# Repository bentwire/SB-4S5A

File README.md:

# SB-4S5A
4S1P 5000mAh smart battery

BOM: https://octopart.com/bom-tool/Ozuqnvew

![Image](https://lh3.googleusercontent.com/idjTSfCK8nfJFQzJIe7masI_trXQ7SMNvU6aqpUEBDsLIDIV-Hx3-JUPBGiGlPwAxTNEt7CckAo6dX-KWBZ0Mj_Hy6Guh6XXaXnfHWQ1HlrcL2ksQrWs3JgNRiBP9fyepqlfmhmZ2Kqe8utfv8-hr5f317K1JAQZiNnnJVtptgWgTnRBBOKp0zHjc3gDmaQTty2snsGGvR-t9d62PkFt3sAev27TS6WXzIwooHEbv2O3aN5GzwUc1_t97cg4gHyUgt0wO-D-wl_EM5B_Wx8xKgb3qa49QhaQvJhumIF56lDGn5g6sMpIpR3Uu-dUa1wRXa-HVk5tHxTNSXTCNnU1kgC_ebQERQPmjxoH67TADfJSTNa7XRiODJmf_CTr2TFzn8DMkGfC8BoBJ0X80usX03oGiI0V0uVGz-C7VfemFuEn6kE7K-gLMqWdNlwAt6iFMoFxGl0MOFubE6W7V08FnX0HrfcozMMg8dFBLveCm-QEvQhAoUhDco0joryzj_BHuwoiUDw_kgubxxIr_FZ4HCkC-sIuyp77qNHq5hAkarBPJ5yDwpvwfY6QkSCwr4eLbbmDiR7ImRQkwWTvxxCPkVSV9cAZq1OyEo_i0pI=w680-h916-no)

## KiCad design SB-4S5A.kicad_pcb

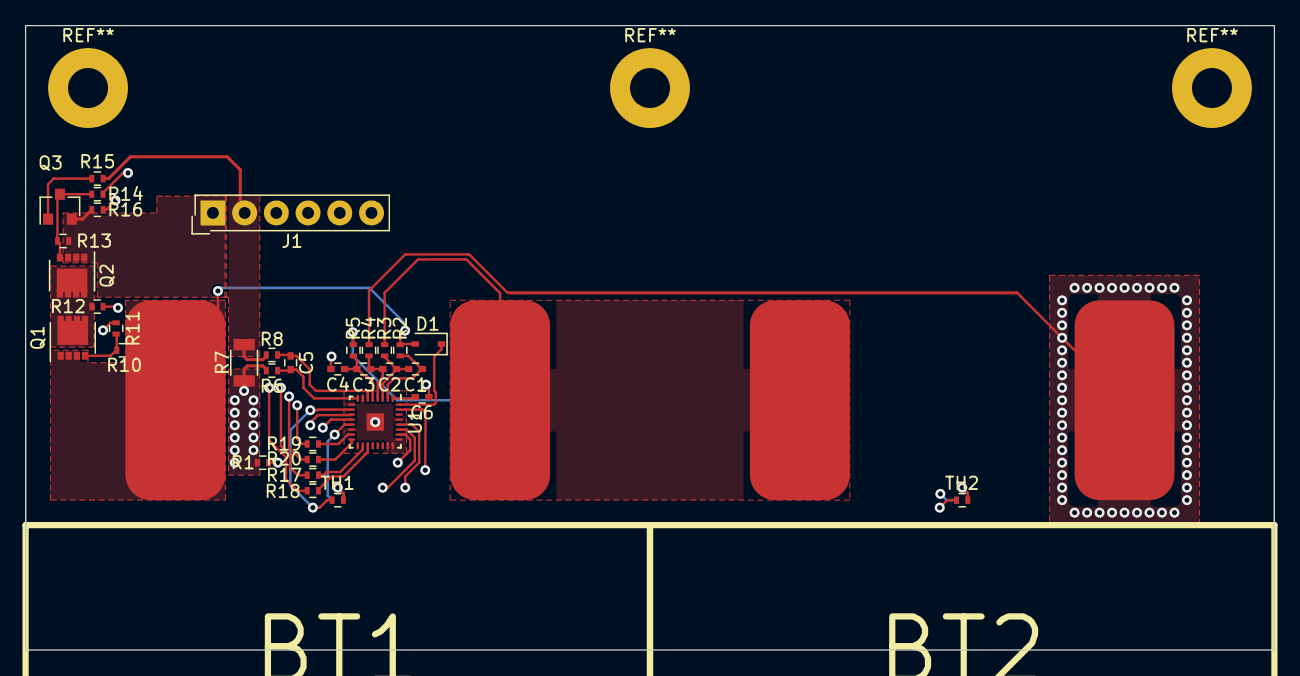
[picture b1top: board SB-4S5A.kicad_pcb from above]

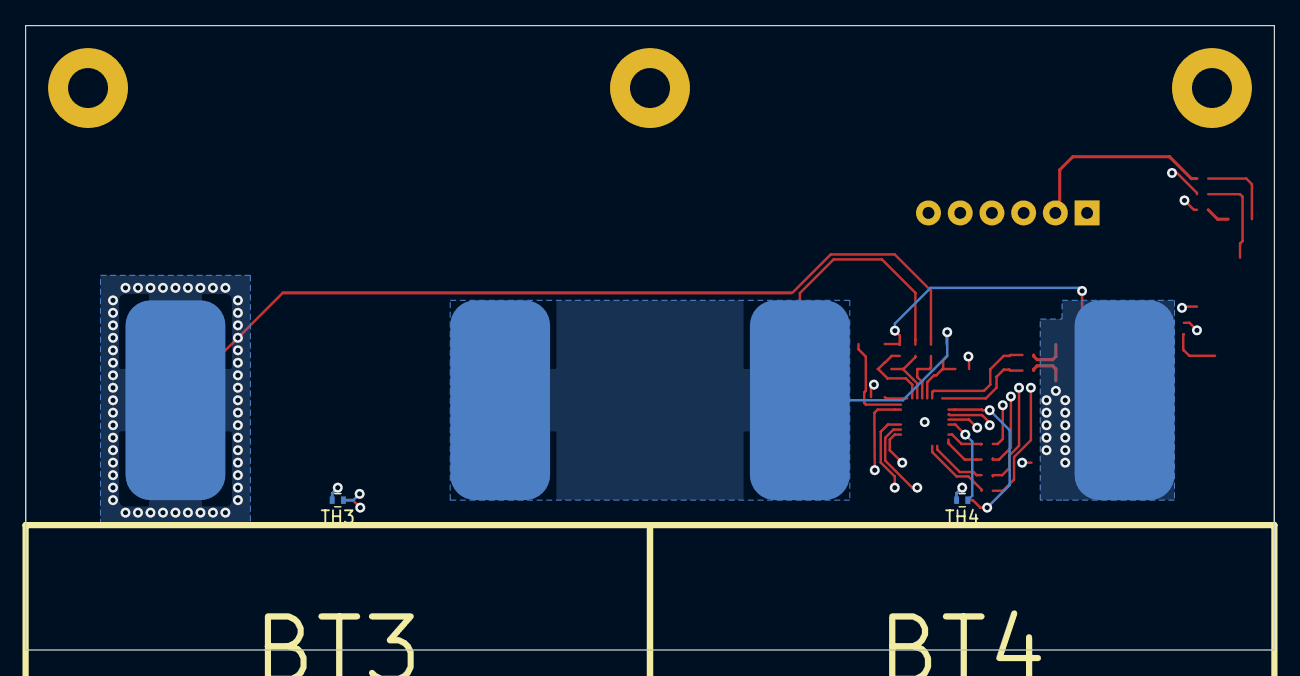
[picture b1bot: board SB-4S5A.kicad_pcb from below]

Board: 4 copper layers, 100.0 x 50.0 mm, 39 parts (4 on the bottom side), 36 nets.

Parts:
BT1, BT2, BT3, BT4: 3.7v; 105070
C1, C2, C3, C4, C5: 0.1u; C_0402
C6: 2.2u; C_0402
D1: BAT54HT1G; D_SOD-323
J1: LEMO6; SL-106-X-XX_1x06
Q1, Q2: CSD17308Q3; VSON-8_3.3x3.3mm_Pitch0.65mm_NexFET
Q3: 2N7002; SOT-23
R1: NET-TIE; R_0402
R2, R3, R4, R5, R6, R8, R12, R17, R18, R19, R20: 100R; R_0402
R7: 0.001R; R_1206
R10, R13: 10M; R_0402
R11, R14: 5.1K; R_0402
R15, R16: 10K; R_0402
TH1, TH2, TH3, TH4: 10K; R_0402
U1: bq40z50-r2; QFN-32_EP_3.8x3.8_Pitch0.4mm

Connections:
/BAT: D1.1, U1.32
/BAT+: BT1.1, D1.2, Q1.1, Q1.2, Q1.3, R2.1, R10.2
/BAT-: BT4.2, R1.1, R6.1, R7.2
/BTP_INT: J1.6, R19.2
/BTP_INT_: R19.1, U1.15
/CHG: R11.1, U1.31
/CHG_G: Q1.4, R10.1, R11.2
/DSG: R14.1, U1.28
/DSG_G: Q2.4, Q3.3, R13.1, R14.2
/MID: Q1.5, Q2.5, R12.2
/PACK: R16.2, U1.27
/PBI: C6.1, U1.1
/SMBC: J1.3, R18.2
/SMBC_: R18.1, U1.19
/SMBD: J1.4, R17.2
/SMBD_: R17.1, U1.18
/SRN: C5.1, R8.2, U1.6
/SRP: C5.2, R6.2, U1.8
/VC1: C3.2, C4.1, R5.2, U1.5
/VC1A: BT3.2, BT4.1, R5.1
/VC2: C2.2, C3.1, R4.2, U1.4
/VC2A: BT2.2, BT3.1, R4.1
/VC3: C1.2, C2.1, R3.2, U1.3
/VC3A: BT1.2, BT2.1, R3.1
/VC4: C1.1, R2.2, U1.2
/_VCC_: R12.1, U1.26
/~PRES/SHDN~_: R20.1, U1.16
/~PRES~: J1.5, R20.2
GNDD: C4.2, C6.2, R1.2, TH1.2, TH2.2, TH3.2, TH4.2, U1.7, U1.9, U1.14, U1.23, U1.24, U1.25, U1.29, U1.33
unnamed: Q3.1, R15.1
unnamed: TH1.1, U1.10
unnamed: TH2.1, U1.11
unnamed: TH3.1, U1.12
unnamed: TH4.1, U1.13
PACK+: J1.1, Q2.1, Q2.2, Q2.3, Q3.2, R13.2, R16.1
PACK-: J1.2, R7.1, R8.1, R15.2

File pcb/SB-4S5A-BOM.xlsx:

Qty | Line Item | Manufacturer | MPN | Octopart URL | Schematic Reference | Internal Part Number | Description | Total Qty (@ Batch Size: 10) | SKU | SKU | Packaging | Packaging | Unit Price (@ Batch Size: 10) | Unit Price (@ Batch Size: 10) | In Stock | In Stock | MOQ | MOQ | URL | URL | Distributor [Custom] | SKU [Custom] | Packaging [Custom] | Unit Price (@ Batch Size: 10) [Custom] | Line Total [Custom] | Batch Total [Custom] | In Stock [Custom] | MOQ [Custom] | URL [Custom] | Notes
 |  |  |  |  |  |  |  |  | Digi-Key | Mouser | Digi-Key | Mouser | Digi-Key | Mouser | Digi-Key | Mouser | Digi-Key | Mouser | Digi-Key | Mouser
2 | CSD17308Q3 | Texas Instruments | CSD17308Q3 | https://octopart.com/csd17308q3-texas+instruments-18530280 | Q1,Q2 |  |  | 20 | 296-27210-1-ND | CSD17308Q3 | Cut Tape |  | 0.904 | 0.676 | 23856 | 56 | 1 |  | https://octopart.com/click/track?country=US&ak=68b25f31&sig=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 | https://octopart.com/click/track?country=US&ak=68b25f31&sig=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 | Mouser | CSD17308Q3 |  | 0.676 | 1.352 | 13.52 | 56 |  | https://octopart.com/click/track?country=US&ak=68b25f31&sig=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
1 | BQ40Z50RSMT-R1 | Texas Instruments | BQ40Z50RSMT-R1 | https://octopart.com/bq40z50rsmt-r1-texas+instruments-60770459 | U1 |  |  | 10 | 296-42424-1-ND | BQ40Z50RSMT-R1 | Cut Tape |  | 5.379 | 5.79 | 0 | 8385 | 1 |  | https://octopart.com/click/track?country=US&ak=68b25f31&sig=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 | https://octopart.com/click/track?country=US&ak=68b25f31&sig=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 | Digi-Key | 296-42424-1-ND | Cut Tape | 5.379 | 5.379 | 53.79 | 0 | 1 | https://octopart.com/click/track?country=US&ak=68b25f31&sig=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
1 | 0.001 ohm 1% 1206 | Welwyn | LRMAM1206-R001FT5 | https://octopart.com/lrmam1206-r001ft5-welwyn-46392712 | R7 |  |  | 10 | 985-1544-1-ND | LRMAM1206-R001FT5 | Cut Tape |  | 0.404 | 0.38 | 5193 | 8269 | 1 |  | https://octopart.com/click/track?country=US&ak=68b25f31&sig=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 | https://octopart.com/click/track?country=US&ak=68b25f31&sig=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 | Mouser | LRMAM1206-R001FT5 |  | 0.38 | 0.38 | 3.8 | 8269 |  | https://octopart.com/click/track?country=US&ak=68b25f31&sig=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
2 | 10K 1% 0402 | Yageo | RC0402FR-0710KL | https://octopart.com/rc0402fr-0710kl-yageo-55458461 | R15,R16 |  |  | 20 | 311-10.0KLRCT-ND | RC0402FR-0710KL | Cut Tape |  | 0.014 | 0.009 | 14082327 | 2372862 | 1 |  | https://octopart.com/click/track?country=US&ak=68b25f31&sig=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 | https://octopart.com/click/track?country=US&ak=68b25f31&sig=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 | Mouser | RC0402FR-0710KL |  | 0.009 | 0.018 | 0.18 | 2372862 |  | https://octopart.com/click/track?country=US&ak=68b25f31&sig=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
2 | 5.1K 1% 0402 | Yageo | RC0402FR-075K1L | https://octopart.com/rc0402fr-075k1l-yageo-39844409 | R11,R14 |  |  | 20 | 311-5.10KLRCT-ND | RC0402FR-075K1L | Cut Tape |  | 0.014 | 0.009 | 1326600 | 308293 | 1 |  | https://octopart.com/click/track?country=US&ak=68b25f31&sig=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 | https://octopart.com/click/track?country=US&ak=68b25f31&sig=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 | Mouser | RC0402FR-075K1L |  | 0.009 | 0.018 | 0.18 | 308293 |  | https://octopart.com/click/track?country=US&ak=68b25f31&sig=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
11 | 100 ohm 1% 0402 | Yageo | RC0402FR-07100RL | https://octopart.com/rc0402fr-07100rl-yageo-40952494 | R2,R3,R4,R5,R6,R8,R12,R17,R18,R19,R20 |  |  | 110 | 311-100LRCT-ND | RC0402FR-07100RL | Cut Tape |  | 0.0056 | 0.003 | 10041531 | 146034 | 1 |  | https://octopart.com/click/track?country=US&ak=68b25f31&sig=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 | https://octopart.com/click/track?country=US&ak=68b25f31&sig=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 | Digi-Key | 311-100LRCT-ND | Cut Tape | 0.0056 | 0.0616 | 0.616 | 10041531 | 1 | https://octopart.com/click/track?country=US&ak=68b25f31&sig=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
2 | 10M 5% 0402 | Yageo | RC0402FR-0710ML | https://octopart.com/rc0402fr-0710ml-yageo-42336635 | R10,R13 |  |  | 20 | 311-10.0MLRCT-ND | RC0402FR-0710ML | Cut Tape |  | 0.013 | 0.01 | 530653 | 92341 | 1 |  | https://octopart.com/click/track?country=US&ak=68b25f31&sig=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 | https://octopart.com/click/track?country=US&ak=68b25f31&sig=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 | Mouser | RC0402FR-0710ML |  | 0.01 | 0.02 | 0.2 | 92341 |  | https://octopart.com/click/track?country=US&ak=68b25f31&sig=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
4 | NTC THERMISTOR 10K OHM 1% 0402 | Murata | NCP15XH103F03RC | https://octopart.com/ncp15xh103f03rc-murata-746463 | TH1, TH2, TH3, TH4 |  |  | 40 | 490-4801-1-ND | NCP15XH103F03RC | Cut Tape |  | 0.0988 | 0.107 | 315244 | 140120 | 1 |  | https://octopart.com/click/track?country=US&ak=68b25f31&sig=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 | https://octopart.com/click/track?country=US&ak=68b25f31&sig=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 | Digi-Key | 490-4801-1-ND | Cut Tape | 0.0988 | 0.3952 | 3.952 | 315244 | 1 | https://octopart.com/click/track?country=US&ak=68b25f31&sig=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
1 | BAT54HT1G | ON Semiconductor | BAT54HT1G | https://octopart.com/bat54ht1g-on+semiconductor-39616 | D1 |  |  | 10 | BAT54HT1GOSCT-ND | BAT54HT1G | Cut Tape |  | 0.225 | 0.167 | 150710 | 19391 | 1 |  | https://octopart.com/click/track?country=US&ak=68b25f31&sig=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 | https://octopart.com/click/track?country=US&ak=68b25f31&sig=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 | Mouser | BAT54HT1G |  | 0.167 | 0.167 | 1.67 | 19391 |  | https://octopart.com/click/track?country=US&ak=68b25f31&sig=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
1 | 2V7002LT1G | ON Semiconductor | 2V7002LT1G | https://octopart.com/2v7002lt1g-on+semiconductor-22133360 | Q3 |  |  | 10 | 2V7002LT1GOSCT-ND | 2V7002LT1G | Cut Tape |  | 0.251 | 0.16 | 100230 | 11900 | 1 |  | https://octopart.com/click/track?country=US&ak=68b25f31&sig=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 | https://octopart.com/click/track?country=US&ak=68b25f31&sig=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 | Digi-Key | 2V7002LT1GOSCT-ND | Cut Tape | 0.251 | 0.251 | 2.51 | 100230 | 1 | https://octopart.com/click/track?country=US&ak=68b25f31&sig=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
1 | 0 ohm jumper 0402 | Yageo | RC0402JR-070RL | https://octopart.com/rc0402jr-070rl-yageo-55434392 | R1 |  |  | 10 | 311-0.0JRCT-ND | RC0402JR-070RL | Cut Tape |  | 0.01 | 0.009 | 0 | 1889345 | 1 |  | https://octopart.com/click/track?country=US&ak=68b25f31&sig=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 | https://octopart.com/click/track?country=US&ak=68b25f31&sig=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 | Mouser | RC0402JR-070RL |  | 0.009 | 0.009 | 0.09 | 1889345 |  | https://octopart.com/click/track?country=US&ak=68b25f31&sig=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
5 | 0.1uF 25V X5R/X7R | TDK | C1005X5R1H104K050BB | https://octopart.com/c1005x5r1h104k050bb-tdk-25947547 | C1,C2,C3,C4,C5 |  |  | 10 | 445-5942-1-ND | C1005X5R1H104K050BB | Cut Tape |  | 0.093 | 0.091 | 3757988 | 146262 | 1 |  | https://octopart.com/click/track?country=US&ak=68b25f31&sig=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 | https://octopart.com/click/track?country=US&ak=68b25f31&sig=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 | Mouser | C1005X5R1H104K050BB |  | 0.091 | 0.091 | 0.91 | 146262 |  | https://octopart.com/click/track?country=US&ak=68b25f31&sig=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
1 | 2.2uF 10V X5R/X7R | Murata | GCM1555C1H680JA16D | https://octopart.com/gcm1555c1h680ja16d-murata-7894738 | C6 |  |  | 10 | 490-12653-1-ND | GCM1555C1H680JA16D | Cut Tape |  | 0.05 | 0.052 | 55591 | 43435 | 1 |  | https://octopart.com/click/track?country=US&ak=68b25f31&sig=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 | https://octopart.com/click/track?country=US&ak=68b25f31&sig=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 | Digi-Key | 490-12653-1-ND | Cut Tape | 0.05 | 0.05 | 0.5 | 55591 | 1 | https://octopart.com/click/track?country=US&ak=68b25f31&sig=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
34

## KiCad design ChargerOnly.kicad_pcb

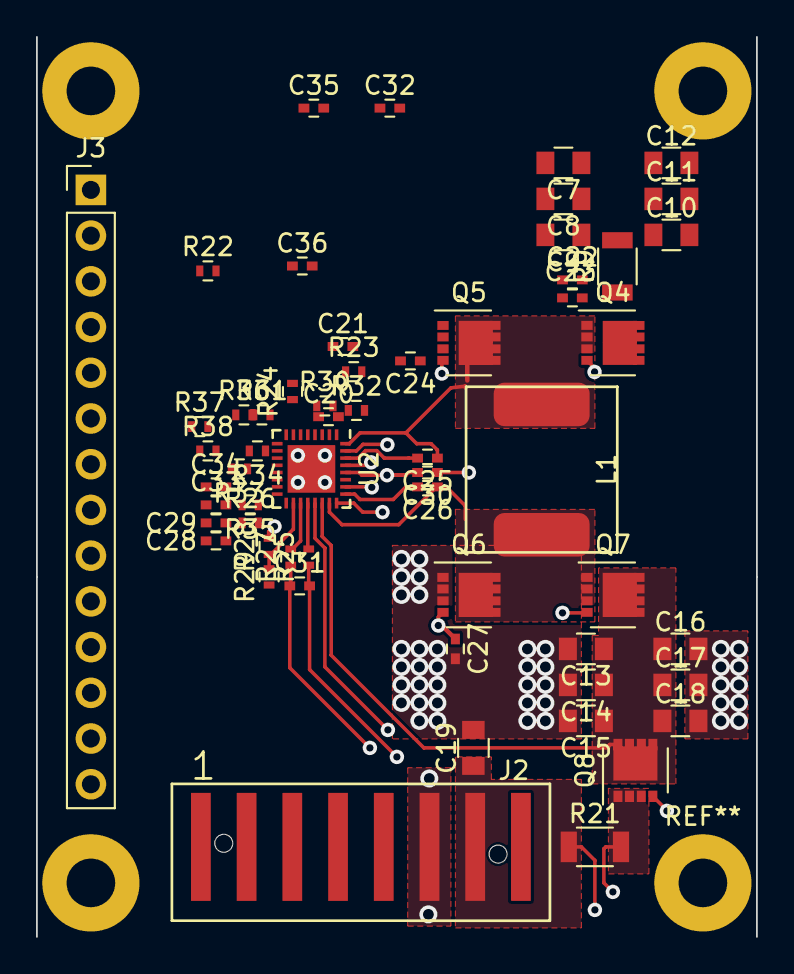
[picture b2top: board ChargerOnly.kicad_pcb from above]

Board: 4 copper layers, 40.0 x 50.0 mm, 58 parts (0 on the bottom side), 35 nets.

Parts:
C7, C8, C9, C10, C11, C12, C13, C14, C15, C16, C17, C18: 10uF; C_0805
C19: 10uF 25V; C_0805
C20, C21: 0.033uF; C_0402
C22: 0.01uF; C_0402
C23: 0.001uF; C_0402
C24, C27: 150pF; C_0402
C25, C26: 0.047uF; C_0402
C28: 15pF; C_0402
C29: 680pF; C_0402
C30: 2.2uF; C_0402
C31: 0.1uF; C_0402
C32: 1uF; C_0402
C33: 33pF; C_0402
C34: 1800pF; C_0402
C35, C36: 100pF; C_0402
J2: Conn_01x06; 14110613002XXX
J3: Conn_01x14; Pin_Header_Straight_1x14_Pitch2.54mm
L1: 2.2uH; WE-LHMI-8030
Q4, Q5, Q6, Q7: CSD17309Q3; VSON-8_3.3x3.3mm_Pitch0.65mm_NexFET
Q8: P-FET; VSON-8_3.3x3.3mm_Pitch0.65mm_NexFET
R9, R21: 0.010R; R_1206
R22, R23: 4.99R; R_0402
R24, R25, R27: 10R 1%; R_0402
R26, R32, R33, R34, R36: 10K 1%; R_0402
R28: 100K 1%; R_0402
R29: 301K 1%; R_0402
R30: 383K 1%; R_0402
R31: 220K 1%; R_0402
R35: 40.2K 1%; R_0402
R37, R38: 137K 1%; R_0402
U2: bq27500A; QFN-32-1EP_4x4mm_Pitch0.4mm

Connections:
/Charger/ACN: C21.1, R23.2, U2.2
/Charger/ACP: C20.1, R22.2, U2.3
/Charger/CBP: R28.1, R29.2, U2.18
/Charger/CHRG_OK: R32.1, U2.4
/Charger/COMP1: C34.2, R35.1, U2.16
/Charger/COMP2: C28.1, R26.2, U2.17
/Charger/IADPT: C36.2, R38.2, U2.8
/Charger/IBAT: C35.1, U2.9
/Charger/ILIM_HIZ: R30.1, R31.2, U2.6
/Charger/L1-L: C25.1, L1.2, Q4.1, Q4.2, Q4.3, Q5.5, U2.32
/Charger/L1-R: C26.1, L1.1, Q6.5, Q7.1, Q7.2, Q7.3, U2.23
/Charger/PSYS: R37.1, U2.10
/Charger/REGN: C30.2, R24.2, R28.2, U2.28
/Charger/SCL: R34.1, U2.13
/Charger/SDA: R33.1, U2.12
/Charger/SRN: R27.2, U2.19
/Charger/SRP: R25.2, U2.20
/Charger/VBAT: C19.1, C31.1, J2.6, R21.1, R27.1
/Charger/VBUS: C7.1, C8.1, C9.1, C10.1, C11.1, C12.1, R9.2, R22.1
/Charger/VDDA: C32.2, R24.1, R30.2, U2.7
/Charger/VSYS: C13.1, C14.1, C15.1, C16.1, C17.1, C18.1, Q7.5, Q8.5, U2.22
/Charger/~BATDRV~: Q8.4, U2.21
/Charger/~PROCHOT~: R36.1, U2.11
GND: C7.2, C8.2, C9.2, C10.2, C11.2, C12.2, C13.2, C14.2, C15.2, C16.2, C17.2, C18.2, C19.2, C20.2, C21.2, C22.1, C23.1, C24.2, C27.2, C28.2, C29.2, C30.1, C32.1, C33.1, C34.1, C35.2, C36.1, J2.5, Q5.1, Q5.2, Q5.3, Q6.1, Q6.2, Q6.3, R29.1, R31.1, R37.2, R38.1, U2.14, U2.27, U2.33
unnamed: C22.2, C23.2, Q4.5, R9.1, R23.1, U2.1
unnamed: C24.1, Q5.4, U2.29
unnamed: C25.2, U2.30
unnamed: C26.2, U2.25
unnamed: C27.1, Q6.4, U2.26
unnamed: C29.1, R26.1
unnamed: C31.2, Q8.1, Q8.2, Q8.3, R21.2, R25.1
unnamed: C33.2, R35.2
unnamed: Q4.4, U2.31
unnamed: Q7.4, U2.24
unnamed: R32.2, R33.2, R34.2, R36.2

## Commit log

2017-07-31 Some updates, net-ties and such.
2017-08-07 Added battery footprint
2017-08-07 Started board layout.
2017-08-08 Add simple battery 3d model, more layout.
2017-08-09 Reannotate
2017-08-27 Finish place and routing.
2017-08-27 Fix missing vias on VC2A
2017-08-27 Move kelvin connection for VC3A to the correct place.
2018-01-13 Convert to "KiCad 5.0" format.
    Other stuff
2018-04-03 Almost done, can't freaking decide on a connector...
2018-04-03 Ready to send to manufacturer.
2018-04-05 Sent to manuf
2018-04-10 Add P&P pos file.
2018-06-29 Fix FUSE pin floating.
